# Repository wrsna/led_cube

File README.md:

# led_cube
This is project that was created 2015 with my friend we decided it will be cool to make an 8x8x8 RGB led cube, so we put heads together and figure it out.

All files are created with Eagle software it is more or less schematic and board view and backup files 

there are some images of the finished product and sadly no Arduino code to see it working that is still waiting to be written

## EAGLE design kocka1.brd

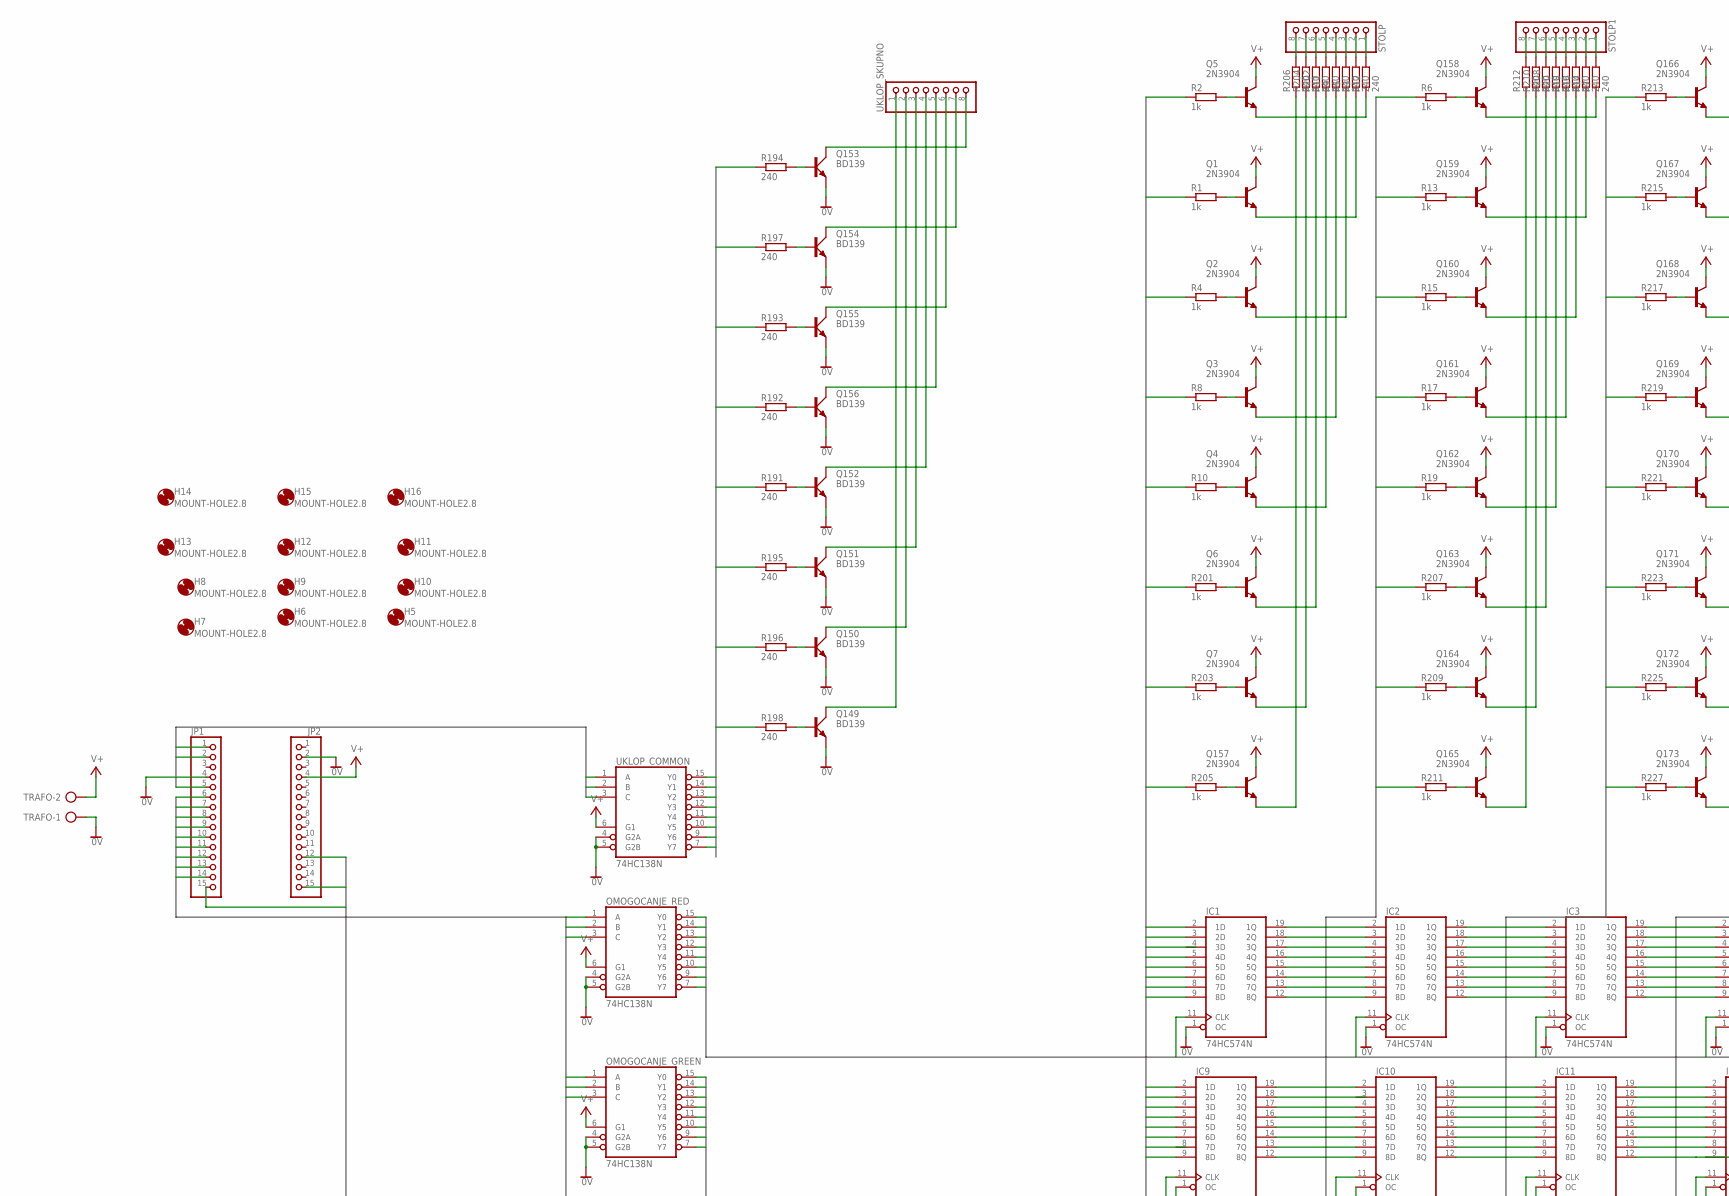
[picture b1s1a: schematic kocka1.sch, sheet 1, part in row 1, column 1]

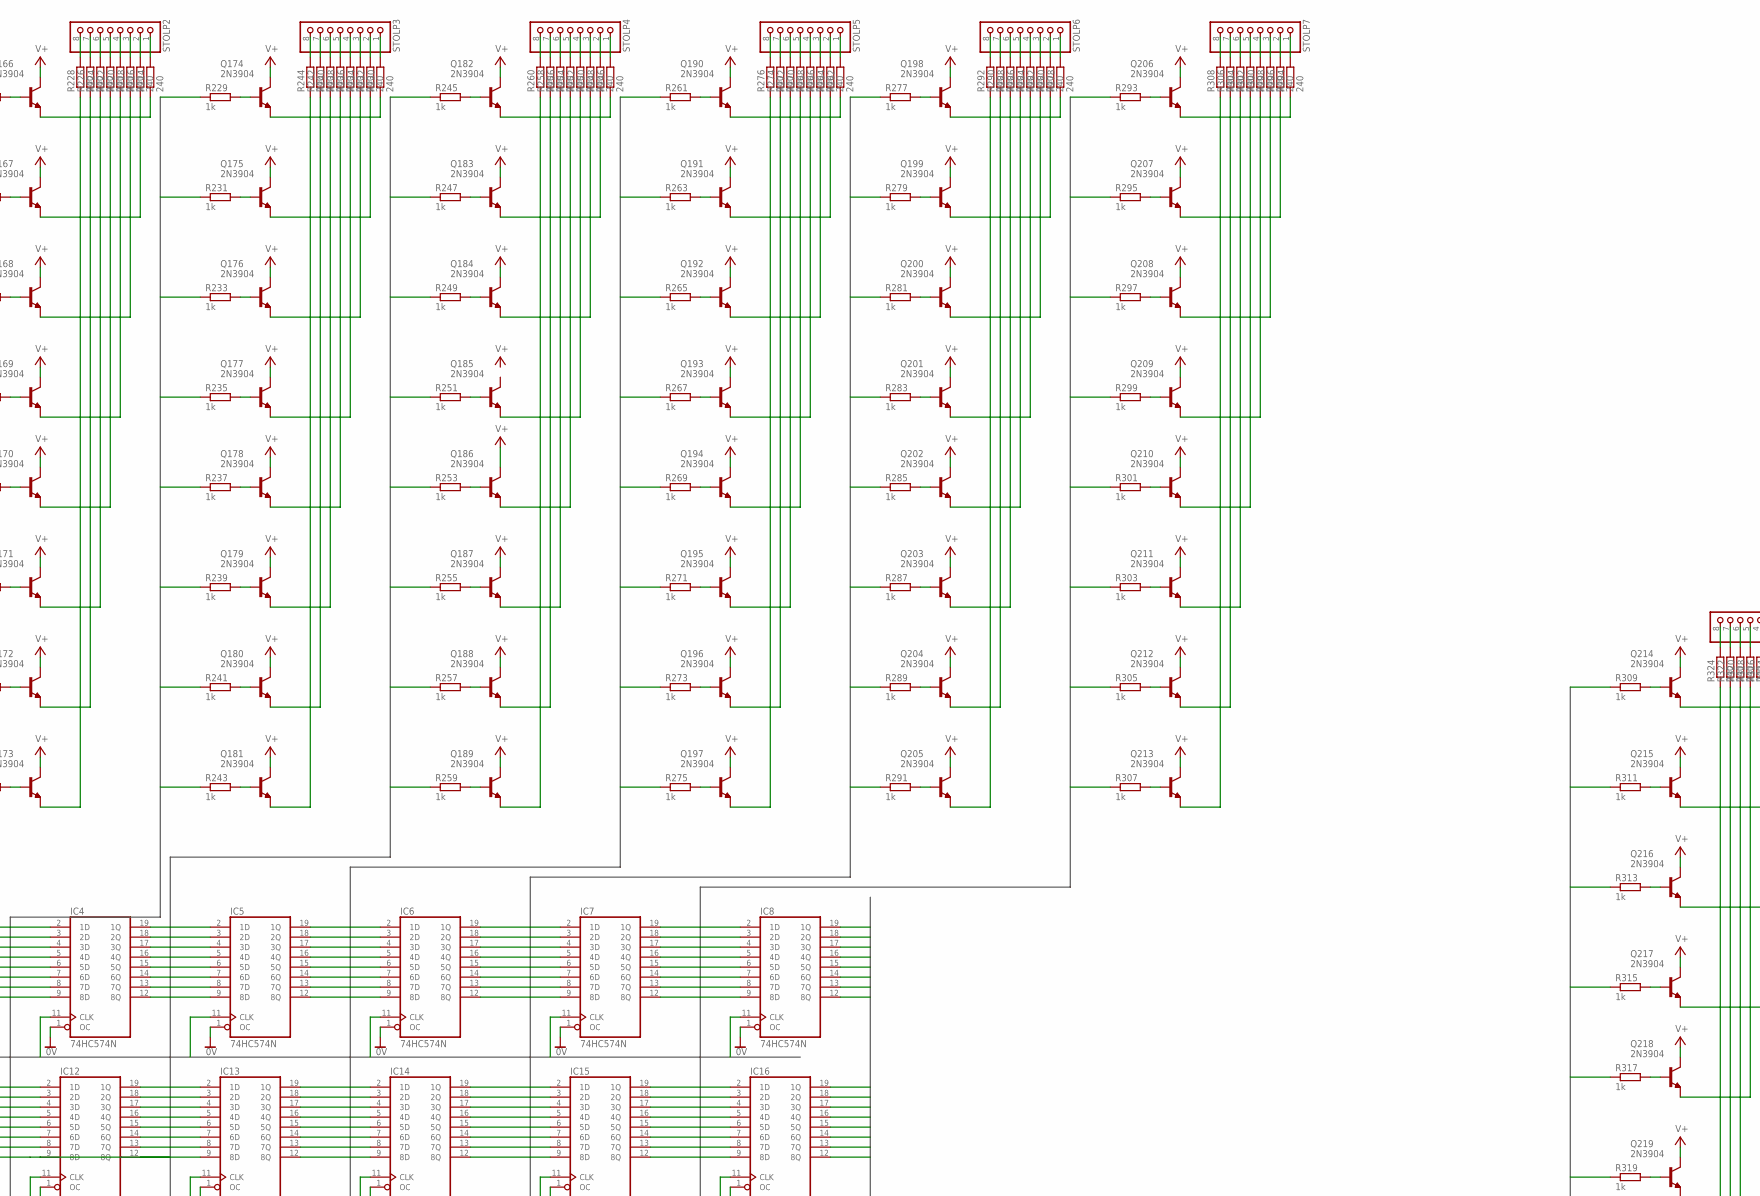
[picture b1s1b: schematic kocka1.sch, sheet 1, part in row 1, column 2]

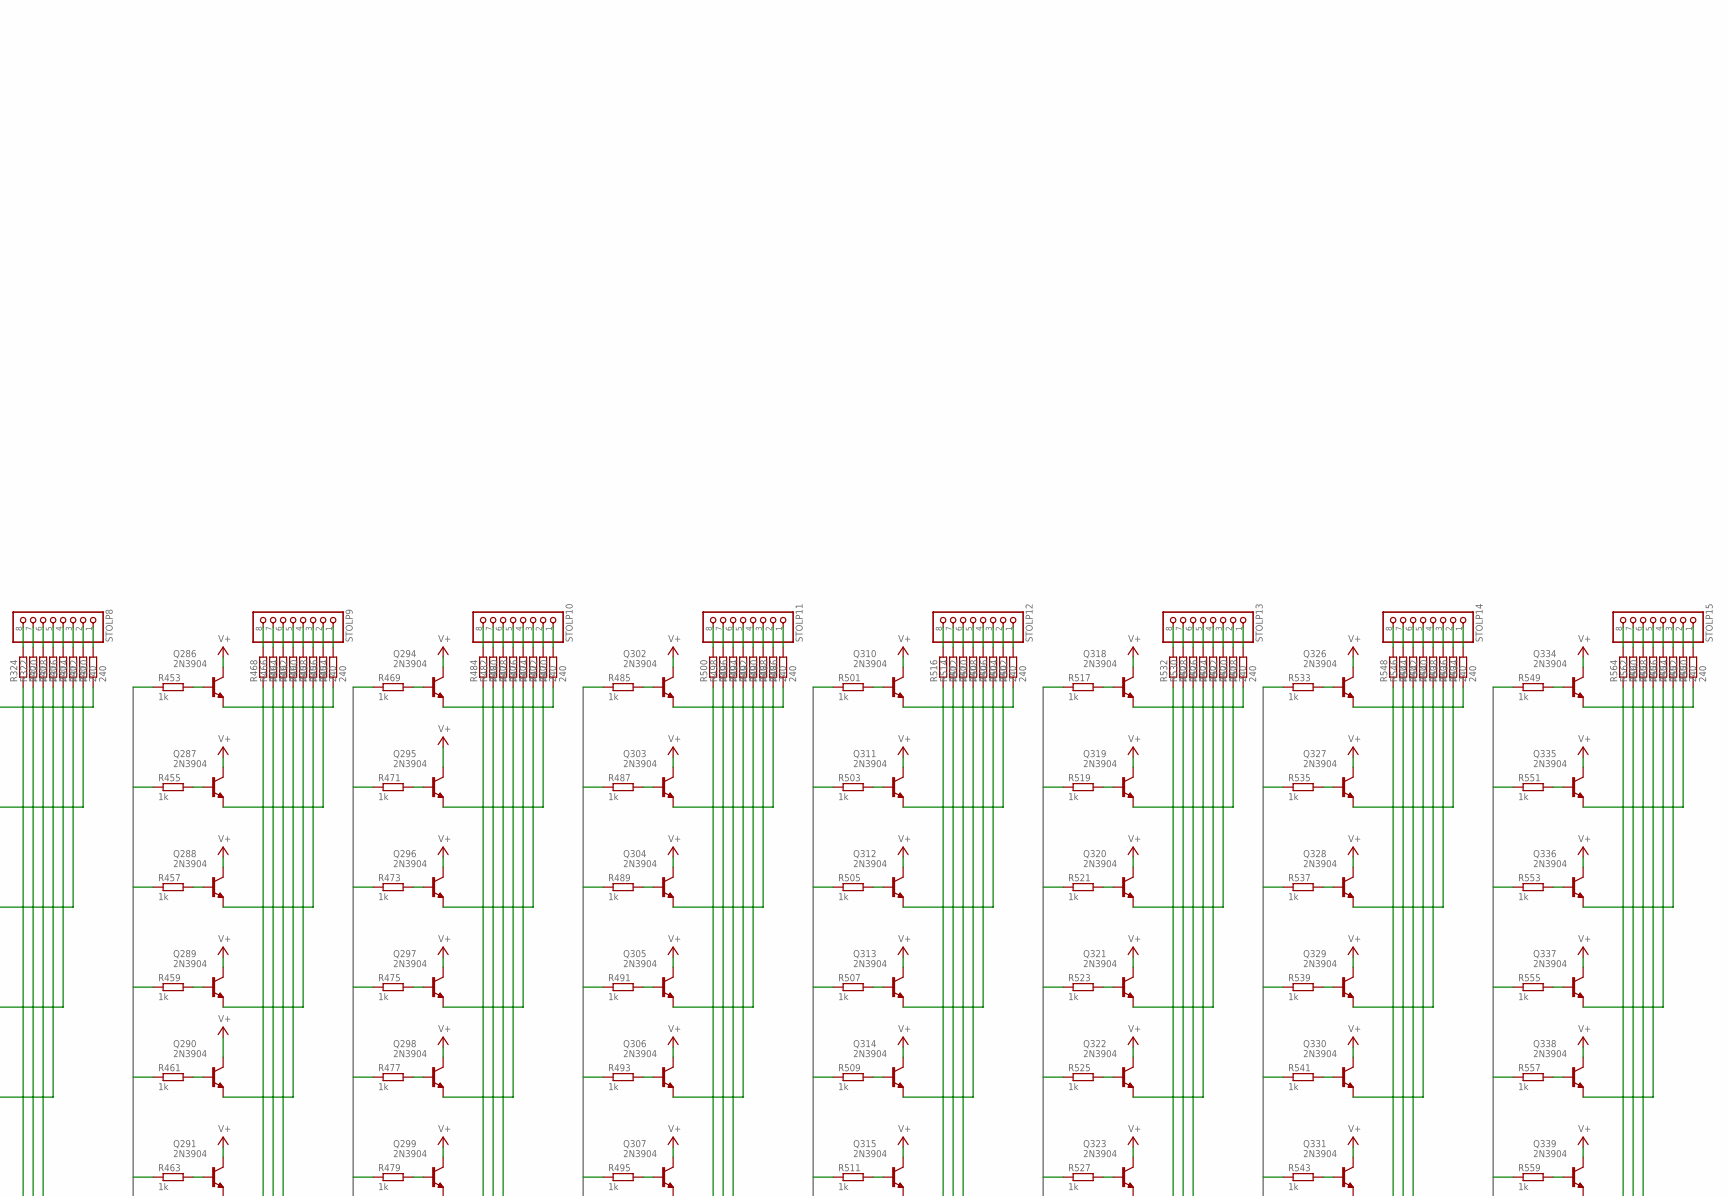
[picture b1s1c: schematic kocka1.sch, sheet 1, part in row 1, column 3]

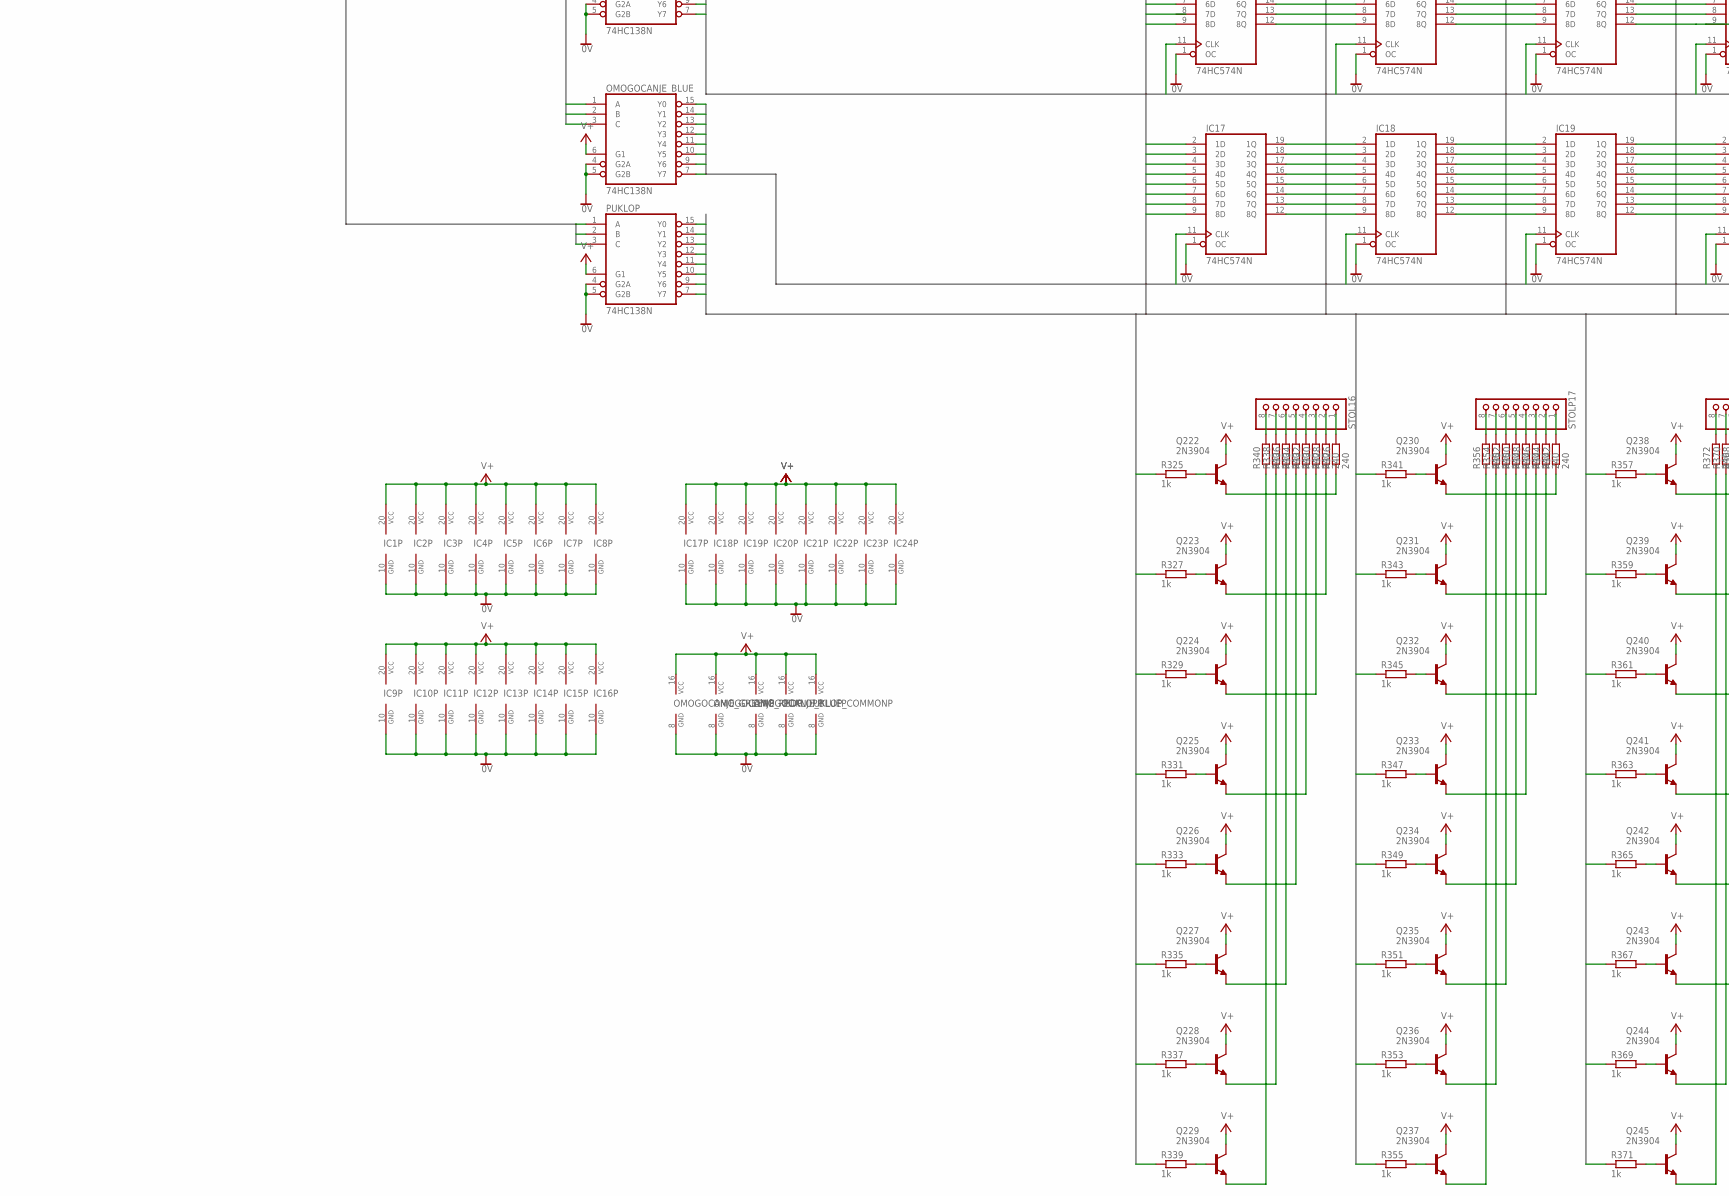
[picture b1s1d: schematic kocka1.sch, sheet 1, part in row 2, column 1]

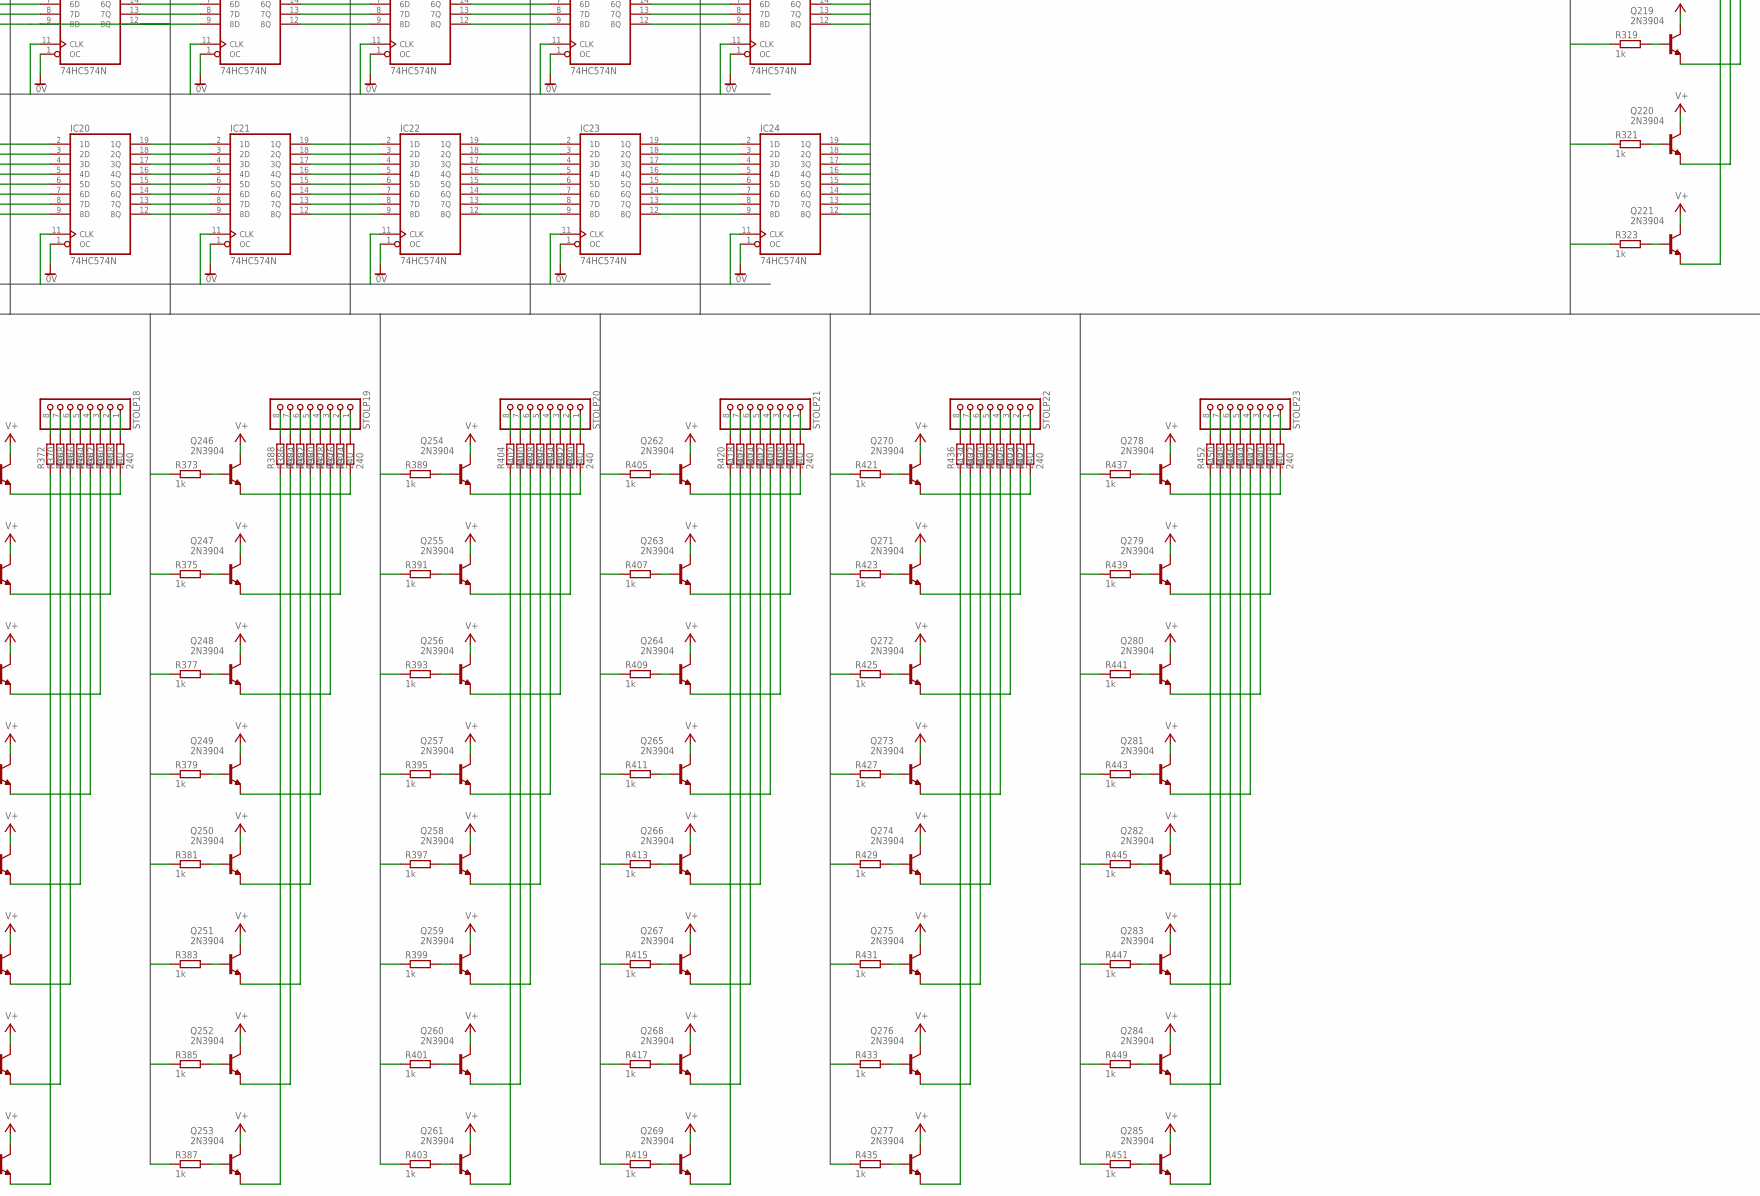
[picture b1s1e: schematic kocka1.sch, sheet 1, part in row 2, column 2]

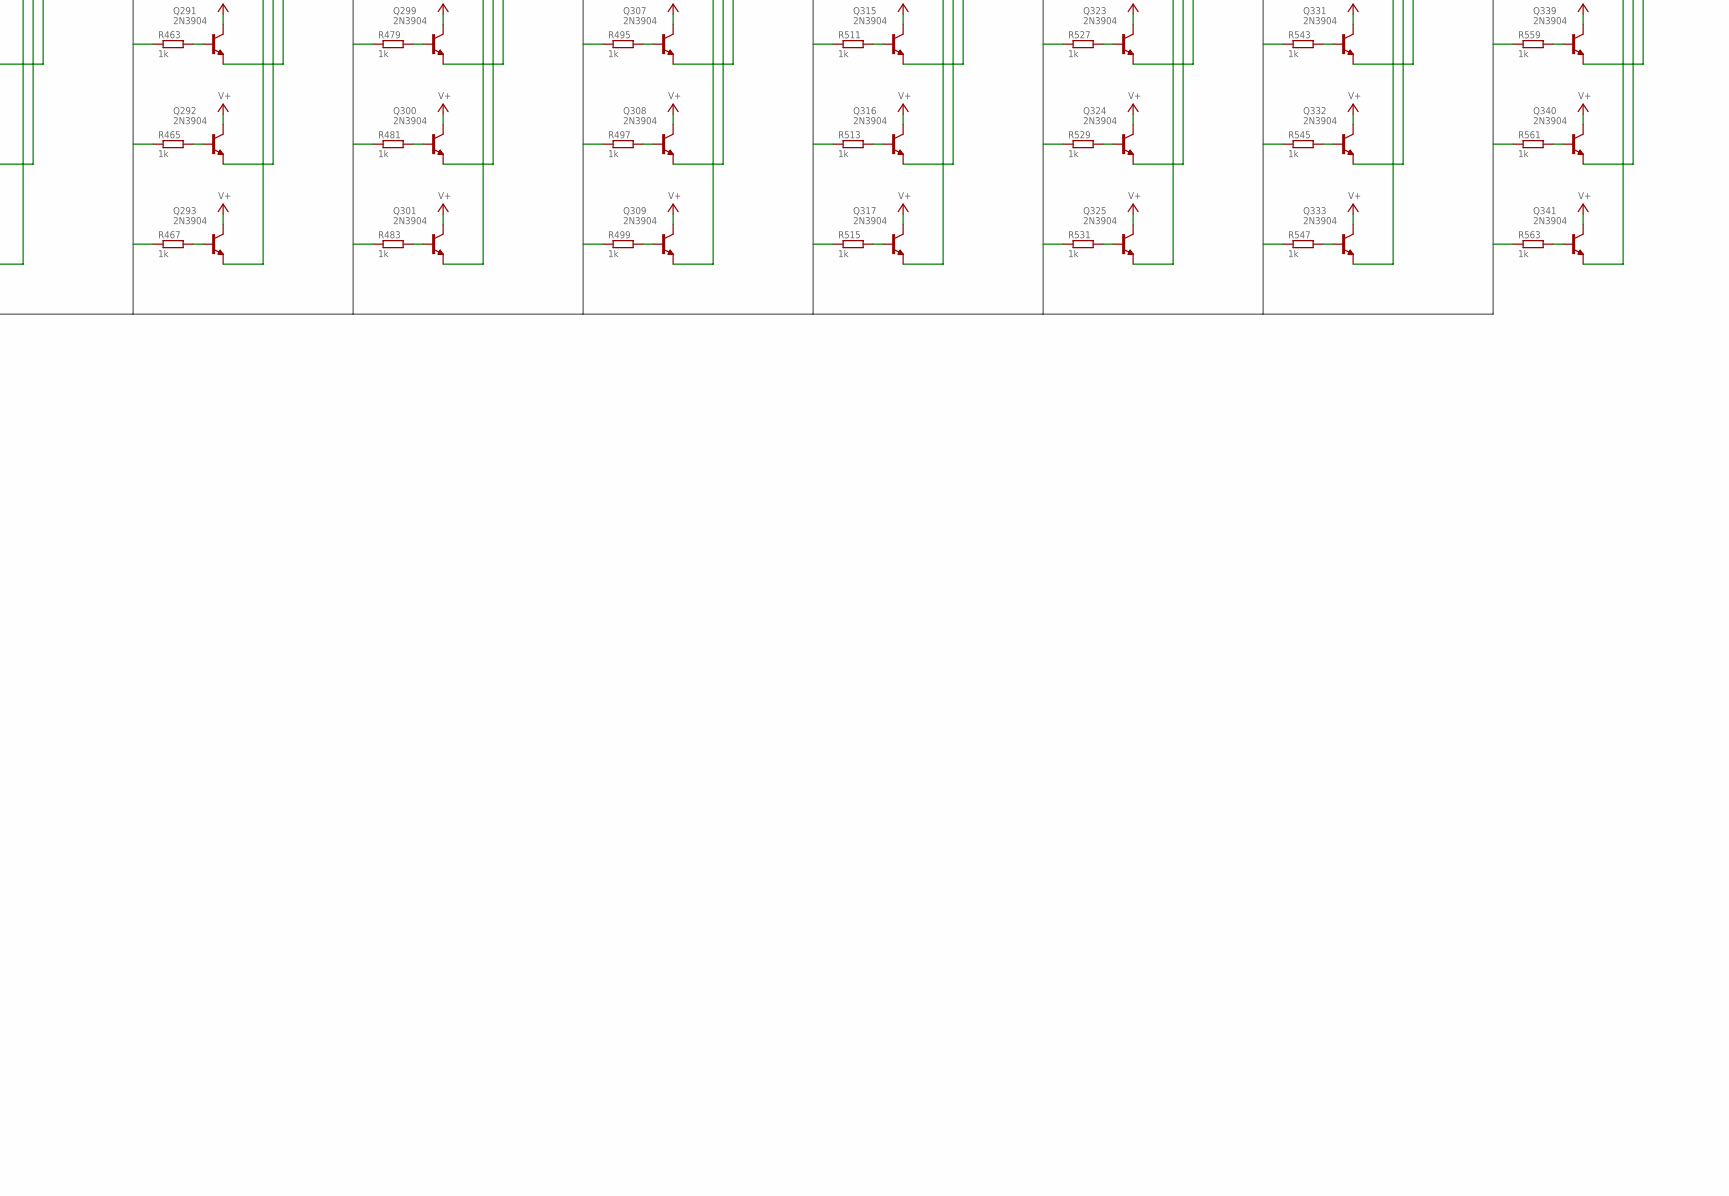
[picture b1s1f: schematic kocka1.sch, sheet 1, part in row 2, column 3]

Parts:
H5, H6, H7, H8, H9, H10, H11, H12, H13, H14, H15, H16: MOUNT-HOLE2.8; 2,8
IC1, IC2, IC3, IC4, IC5, IC6, IC7, IC8, IC9, IC10, IC11, IC12, IC13, IC14, IC15, IC16, IC17, IC18, IC19, IC20, IC21, IC22, IC23, IC24: 74HC574N; DIL20
JP1, JP2: PINHD-1X15; 1X15
OMOGOCANJE_BLUE: 74HC138N; DIL16
OMOGOCANJE_GREEN: 74HC138N; DIL16
OMOGOCANJE_RED: 74HC138N; DIL16
PUKLOP: 74HC138N; DIL16
Q1, Q2, Q3, Q4, Q5, Q6, Q7, Q157, Q158, Q159, Q160, Q161, Q162, Q163, Q164, Q165, Q166, Q167, Q168, Q169, Q170, Q171, Q172, Q173, Q174, Q175, Q176, Q177, Q178, Q179, Q180, Q181, Q182, Q183, Q184, Q185, Q186, Q187, Q188, Q189, Q190, Q191, Q192, Q193, Q194, Q195, Q196, Q197, Q198, Q199, Q200, Q201, Q202, Q203, Q204, Q205, Q206, Q207, Q208, Q209, Q210, Q211, Q212, Q213, Q214, Q215, Q216, Q217, Q218, Q219, Q220, Q221, Q222, Q223, Q224, Q225, Q226, Q227, Q228, Q229, Q230, Q231, Q232, Q233, Q234, Q235, Q236, Q237, Q238, Q239, Q240, Q241, Q242, Q243, Q244, Q245, Q246, Q247, Q248, Q249, Q250, Q251, Q252, Q253, Q254, Q255, Q256, Q257, Q258, Q259, Q260, Q261, Q262, Q263, Q264, Q265, Q266, Q267, Q268, Q269, Q270, Q271, Q272, Q273, Q274, Q275, Q276, Q277, Q278, Q279, Q280, Q281, Q282, Q283, Q284, Q285, Q286, Q287, Q288, Q289, Q290, Q291, Q292, Q293, Q294, Q295, Q296, Q297, Q298, Q299, Q300, Q301, Q302, Q303, Q304, Q305, Q306, Q307, Q308, Q309, Q310, Q311, Q312, Q313, Q314, Q315, Q316, Q317, Q318, Q319, Q320, Q321, Q322, Q323, Q324, Q325, Q326, Q327, Q328, Q329, Q330, Q331, Q332, Q333, Q334, Q335, Q336, Q337, Q338, Q339, Q340, Q341: 2N3904; TO92
Q149, Q150, Q151, Q152, Q153, Q154, Q155, Q156: BD139; TO126AV
R1, R2, R4, R6, R8, R10, R13, R15, R17, R19, R201, R203, R205, R207, R209, R211, R213, R215, R217, R219, R221, R223, R225, R227, R229, R231, R233, R235, R237, R239, R241, R243, R245, R247, R249, R251, R253, R255, R257, R259, R261, R263, R265, R267, R269, R271, R273, R275, R277, R279, R281, R283, R285, R287, R289, R291, R293, R295, R297, R299, R301, R303, R305, R307, R309, R311, R313, R315, R317, R319, R321, R323, R325, R327, R329, R331, R333, R335, R337, R339, R341, R343, R345, R347, R349, R351, R353, R355, R357, R359, R361, R363, R365, R367, R369, R371, R373, R375, R377, R379, R381, R383, R385, R387, R389, R391, R393, R395, R397, R399, R401, R403, R405, R407, R409, R411, R413, R415, R417, R419, R421, R423, R425, R427, R429, R431, R433, R435, R437, R439, R441, R443, R445, R447, R449, R451, R453, R455, R457, R459, R461, R463, R465, R467, R469, R471, R473, R475, R477, R479, R481, R483, R485, R487, R489, R491, R493, R495, R497, R499, R501, R503, R505, R507, R509, R511, R513, R515, R517, R519, R521, R523, R525, R527, R529, R531, R533, R535, R537, R539, R541, R543, R545, R547, R549, R551, R553, R555, R557, R559, R561, R563: 1k; 0207/10
R3, R5, R7, R9, R11, R12, R14, R16, R18, R20, R191, R192, R193, R194, R195, R196, R197, R198, R202, R204, R206, R208, R210, R212, R214, R216, R218, R220, R222, R224, R226, R228, R230, R232, R234, R236, R238, R240, R242, R244, R246, R248, R250, R252, R254, R256, R258, R260, R262, R264, R266, R268, R270, R272, R274, R276, R278, R280, R282, R284, R286, R288, R290, R292, R294, R296, R298, R300, R302, R304, R306, R308, R310, R312, R314, R316, R318, R320, R322, R324, R326, R328, R330, R332, R334, R336, R338, R340, R342, R344, R346, R348, R350, R352, R354, R356, R358, R360, R362, R364, R366, R368, R370, R372, R374, R376, R378, R380, R382, R384, R386, R388, R390, R392, R394, R396, R398, R400, R402, R404, R406, R408, R410, R412, R414, R416, R418, R420, R422, R424, R426, R428, R430, R432, R434, R436, R438, R440, R442, R444, R446, R448, R450, R452, R454, R456, R458, R460, R462, R464, R466, R468, R470, R472, R474, R476, R478, R480, R482, R484, R486, R488, R490, R492, R494, R496, R498, R500, R502, R504, R506, R508, R510, R512, R514, R516, R518, R520, R522, R524, R526, R528, R530, R532, R534, R536, R538, R540, R542, R544, R546, R548, R550, R552, R554, R556, R558, R560, R562, R564: 240; 0207/10
STOL16: PINHD-1X8; 1X08
STOLP, STOLP1, STOLP2, STOLP3, STOLP4, STOLP5, STOLP6, STOLP7, STOLP8, STOLP9, STOLP10, STOLP11, STOLP12, STOLP13, STOLP14, STOLP15, STOLP17, STOLP18, STOLP19, STOLP20, STOLP21, STOLP22, STOLP23: PINHD-1X8; 1X08
TRAFO: AK300/2
UKLOP_COMMON: 74HC138N; DIL16
UKLOP_SKUPNO: PINHD-1X8; 1X08

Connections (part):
0V: IC1.1 (OC), IC1.10 (GND), IC2.1 (OC), IC2.10 (GND), IC3.1 (OC), IC3.10 (GND), IC4.1 (OC), IC4.10 (GND), IC5.1 (OC), IC5.10 (GND), IC6.1 (OC), IC6.10 (GND), IC7.1 (OC), IC7.10 (GND), IC8.1 (OC), IC8.10 (GND), IC9.1 (OC), IC9.10 (GND), IC10.1 (OC), IC10.10 (GND), IC11.1 (OC), IC11.10 (GND), IC12.1 (OC), IC12.10 (GND), IC13.1 (OC), IC13.10 (GND), IC14.1 (OC), IC14.10 (GND), IC15.1 (OC), IC15.10 (GND), IC16.1 (OC), IC16.10 (GND), IC17.1 (OC), IC17.10 (GND), IC18.1 (OC), IC18.10 (GND), IC19.1 (OC), IC19.10 (GND), IC20.1 (OC), IC20.10 (GND), IC21.1 (OC), IC21.10 (GND), IC22.1 (OC), IC22.10 (GND), IC23.1 (OC), IC23.10 (GND), IC24.1 (OC), IC24.10 (GND), JP1.4, JP2.2, OMOGOCANJE_BLUE.4 (G2A), OMOGOCANJE_BLUE.5 (G2B), OMOGOCANJE_BLUE.8 (GND), OMOGOCANJE_GREEN.4 (G2A), OMOGOCANJE_GREEN.5 (G2B), OMOGOCANJE_GREEN.8 (GND), OMOGOCANJE_RED.4 (G2A), OMOGOCANJE_RED.5 (G2B), OMOGOCANJE_RED.8 (GND), PUKLOP.4 (G2A), PUKLOP.5 (G2B), PUKLOP.8 (GND), Q149.E, Q150.E, Q151.E, Q152.E, Q153.E, Q154.E, Q155.E, Q156.E, TRAFO.1, UKLOP_COMMON.4 (G2A), UKLOP_COMMON.5 (G2B), UKLOP_COMMON.8 (GND)
COMMON0: JP1.2, UKLOP_COMMON.3 (C)
COMMON1: JP1.1, UKLOP_COMMON.2 (B)
COMMON2: JP1.5, UKLOP_COMMON.1 (A)
unnamed: Q149.B, R198.2
unnamed: Q5.3 (E), R12.1
unnamed: Q150.B, R196.2
unnamed: Q151.B, R195.2
unnamed: Q152.B, R191.2
unnamed: Q156.B, R192.2
unnamed: Q155.B, R193.2
unnamed: Q154.B, R197.2
unnamed: Q153.B, R194.2
unnamed: Q153.C, UKLOP_SKUPNO.8
unnamed: Q154.C, UKLOP_SKUPNO.7
unnamed: Q155.C, UKLOP_SKUPNO.6
unnamed: Q156.C, UKLOP_SKUPNO.5
unnamed: Q152.C, UKLOP_SKUPNO.4
unnamed: Q151.C, UKLOP_SKUPNO.3
unnamed: Q150.C, UKLOP_SKUPNO.2
unnamed: Q149.C, UKLOP_SKUPNO.1
unnamed: Q5.2 (B), R2.2
unnamed: Q1.2 (B), R1.2
unnamed: Q1.3 (E), R3.1
unnamed: Q2.2 (B), R4.2
unnamed: Q2.3 (E), R5.1
unnamed: Q3.2 (B), R8.2
unnamed: Q3.3 (E), R9.1
unnamed: Q4.2 (B), R10.2
unnamed: Q4.3 (E), R11.1
unnamed: Q6.2 (B), R201.2
unnamed: Q6.3 (E), R202.1
unnamed: Q7.2 (B), R203.2
unnamed: Q7.3 (E), R204.1
unnamed: Q157.2 (B), R205.2
unnamed: Q157.3 (E), R206.1
unnamed: Q158.3 (E), R7.1
unnamed: Q159.3 (E), R14.1
unnamed: Q160.3 (E), R16.1
unnamed: Q161.3 (E), R18.1
unnamed: Q162.3 (E), R20.1
unnamed: Q163.3 (E), R208.1
unnamed: Q164.3 (E), R210.1
unnamed: Q165.3 (E), R212.1
unnamed: Q158.2 (B), R6.2
unnamed: R212.2, STOLP1.8
unnamed: Q159.2 (B), R13.2
unnamed: R210.2, STOLP1.7
unnamed: Q160.2 (B), R15.2
unnamed: R208.2, STOLP1.6
unnamed: Q161.2 (B), R17.2
unnamed: R20.2, STOLP1.5
unnamed: Q162.2 (B), R19.2
unnamed: R18.2, STOLP1.4
unnamed: Q163.2 (B), R207.2
unnamed: R16.2, STOLP1.3
unnamed: Q164.2 (B), R209.2
unnamed: R14.2, STOLP1.2
unnamed: Q165.2 (B), R211.2
unnamed: R7.2, STOLP1.1
unnamed: R206.2, STOLP.8
unnamed: R204.2, STOLP.7
unnamed: R202.2, STOLP.6
unnamed: R11.2, STOLP.5
unnamed: R9.2, STOLP.4
unnamed: R5.2, STOLP.3
unnamed: R3.2, STOLP.2
unnamed: R12.2, STOLP.1
unnamed: Q166.2 (B), R213.2
unnamed: R228.2, STOLP2.8
unnamed: Q167.2 (B), R215.2
unnamed: R226.2, STOLP2.7
unnamed: Q168.2 (B), R217.2
unnamed: R224.2, STOLP2.6
unnamed: Q169.2 (B), R219.2
unnamed: R222.2, STOLP2.5
unnamed: Q170.2 (B), R221.2
unnamed: R220.2, STOLP2.4
unnamed: Q171.2 (B), R223.2
unnamed: R218.2, STOLP2.3
unnamed: Q172.2 (B), R225.2
unnamed: R216.2, STOLP2.2
unnamed: Q173.2 (B), R227.2
unnamed: R214.2, STOLP2.1
unnamed: Q166.3 (E), R214.1
unnamed: Q167.3 (E), R216.1
unnamed: Q168.3 (E), R218.1
unnamed: Q169.3 (E), R220.1
unnamed: Q170.3 (E), R222.1
unnamed: Q171.3 (E), R224.1
unnamed: Q172.3 (E), R226.1
unnamed: Q173.3 (E), R228.1
unnamed: Q174.2 (B), R229.2
unnamed: Q174.3 (E), R230.1
unnamed: Q175.2 (B), R231.2
unnamed: R244.2, STOLP3.8
unnamed: Q176.2 (B), R233.2
unnamed: R242.2, STOLP3.7
unnamed: Q177.2 (B), R235.2
unnamed: R240.2, STOLP3.6
unnamed: Q178.2 (B), R237.2
unnamed: R238.2, STOLP3.5
unnamed: Q179.2 (B), R239.2
unnamed: R236.2, STOLP3.4
unnamed: Q180.2 (B), R241.2
unnamed: R234.2, STOLP3.3
unnamed: Q181.2 (B), R243.2
unnamed: R232.2, STOLP3.2
unnamed: R230.2, STOLP3.1
unnamed: Q175.3 (E), R232.1
unnamed: Q176.3 (E), R234.1
unnamed: Q177.3 (E), R236.1
unnamed: Q178.3 (E), R238.1
unnamed: Q179.3 (E), R240.1
unnamed: Q180.3 (E), R242.1
unnamed: Q181.3 (E), R244.1
unnamed: Q182.2 (B), R245.2
unnamed: Q182.3 (E), R246.1
unnamed: Q183.2 (B), R247.2
unnamed: R260.2, STOLP4.8
unnamed: Q184.2 (B), R249.2
unnamed: R258.2, STOLP4.7
unnamed: Q185.2 (B), R251.2
unnamed: R256.2, STOLP4.6
unnamed: Q186.2 (B), R253.2
unnamed: R254.2, STOLP4.5
unnamed: Q187.2 (B), R255.2
unnamed: R252.2, STOLP4.4
unnamed: Q188.2 (B), R257.2
unnamed: R250.2, STOLP4.3
unnamed: Q189.2 (B), R259.2
unnamed: R248.2, STOLP4.2
unnamed: Q183.3 (E), R248.1
unnamed: Q184.3 (E), R250.1
unnamed: R246.2, STOLP4.1
unnamed: Q185.3 (E), R252.1
unnamed: Q186.3 (E), R254.1
unnamed: Q187.3 (E), R256.1
unnamed: Q188.3 (E), R258.1
unnamed: Q189.3 (E), R260.1
unnamed: Q190.2 (B), R261.2
unnamed: R276.2, STOLP5.8
unnamed: Q191.2 (B), R263.2
unnamed: R274.2, STOLP5.7
unnamed: Q192.2 (B), R265.2
unnamed: R272.2, STOLP5.6
unnamed: Q193.2 (B), R267.2
unnamed: R270.2, STOLP5.5
unnamed: Q194.2 (B), R269.2
unnamed: R268.2, STOLP5.4
unnamed: Q195.2 (B), R271.2
unnamed: R266.2, STOLP5.3
unnamed: Q196.2 (B), R273.2
unnamed: R264.2, STOLP5.2
unnamed: Q197.2 (B), R275.2
unnamed: R262.2, STOLP5.1
unnamed: Q190.3 (E), R262.1
unnamed: Q191.3 (E), R264.1
unnamed: Q192.3 (E), R266.1
unnamed: Q193.3 (E), R268.1
unnamed: Q194.3 (E), R270.1
unnamed: Q195.3 (E), R272.1
unnamed: Q196.3 (E), R274.1
unnamed: Q197.3 (E), R276.1
unnamed: Q198.2 (B), R277.2
unnamed: R292.2, STOLP6.8
unnamed: Q199.2 (B), R279.2
unnamed: R290.2, STOLP6.7
unnamed: Q200.2 (B), R281.2
unnamed: R288.2, STOLP6.6
unnamed: Q201.2 (B), R283.2
unnamed: R286.2, STOLP6.5
unnamed: Q202.2 (B), R285.2
unnamed: R284.2, STOLP6.4
unnamed: Q203.2 (B), R287.2
unnamed: R282.2, STOLP6.3
unnamed: Q204.2 (B), R289.2
unnamed: R280.2, STOLP6.2
unnamed: Q205.2 (B), R291.2
unnamed: R278.2, STOLP6.1
unnamed: Q198.3 (E), R278.1
unnamed: Q199.3 (E), R280.1
unnamed: Q200.3 (E), R282.1
unnamed: Q201.3 (E), R284.1
unnamed: Q202.3 (E), R286.1
unnamed: Q203.3 (E), R288.1
unnamed: Q204.3 (E), R290.1
unnamed: Q205.3 (E), R292.1
unnamed: Q206.2 (B), R293.2
unnamed: Q206.3 (E), R294.1
unnamed: Q207.2 (B), R295.2
unnamed: R308.2, STOLP7.8
unnamed: Q208.2 (B), R297.2
unnamed: R306.2, STOLP7.7
unnamed: Q209.2 (B), R299.2
unnamed: R304.2, STOLP7.6
unnamed: Q210.2 (B), R301.2
unnamed: R302.2, STOLP7.5
unnamed: Q211.2 (B), R303.2
unnamed: R300.2, STOLP7.4
unnamed: Q212.2 (B), R305.2
unnamed: R298.2, STOLP7.3
unnamed: Q213.2 (B), R307.2
unnamed: R296.2, STOLP7.2
unnamed: R294.2, STOLP7.1
unnamed: Q207.3 (E), R296.1
unnamed: Q208.3 (E), R298.1
unnamed: Q209.3 (E), R300.1
unnamed: Q210.3 (E), R302.1
unnamed: Q211.3 (E), R304.1
unnamed: Q212.3 (E), R306.1
unnamed: Q213.3 (E), R308.1
unnamed: Q214.2 (B), R309.2
unnamed: R324.2, STOLP8.8
unnamed: Q215.2 (B), R311.2
unnamed: R322.2, STOLP8.7
unnamed: Q216.2 (B), R313.2
unnamed: R320.2, STOLP8.6
unnamed: Q217.2 (B), R315.2
unnamed: R318.2, STOLP8.5
unnamed: Q218.2 (B), R317.2
unnamed: R316.2, STOLP8.4
unnamed: Q219.2 (B), R319.2
unnamed: R314.2, STOLP8.3
unnamed: Q220.2 (B), R321.2
unnamed: R312.2, STOLP8.2
unnamed: Q221.2 (B), R323.2
unnamed: R310.2, STOLP8.1
unnamed: Q214.3 (E), R310.1
unnamed: Q215.3 (E), R312.1
unnamed: Q216.3 (E), R314.1
unnamed: Q217.3 (E), R316.1
unnamed: Q218.3 (E), R318.1
unnamed: Q219.3 (E), R320.1
unnamed: Q220.3 (E), R322.1
unnamed: Q221.3 (E), R324.1
unnamed: Q222.2 (B), R325.2
unnamed: Q286.3 (E), R454.1
unnamed: Q223.2 (B), R327.2
unnamed: R468.2, STOLP9.8
unnamed: Q224.2 (B), R329.2
unnamed: R466.2, STOLP9.7
unnamed: Q225.2 (B), R331.2
unnamed: R464.2, STOLP9.6
unnamed: Q226.2 (B), R333.2
unnamed: R462.2, STOLP9.5
unnamed: Q227.2 (B), R335.2
unnamed: R460.2, STOLP9.4
unnamed: Q228.2 (B), R337.2
unnamed: R458.2, STOLP9.3
unnamed: Q229.2 (B), R339.2
unnamed: R456.2, STOLP9.2
unnamed: R454.2, STOLP9.1
unnamed: Q287.3 (E), R456.1
unnamed: Q288.3 (E), R458.1
unnamed: Q289.3 (E), R460.1
unnamed: Q290.3 (E), R462.1
unnamed: Q291.3 (E), R464.1
unnamed: Q292.3 (E), R466.1
unnamed: Q293.3 (E), R468.1
unnamed: Q230.2 (B), R341.2
unnamed: Q294.3 (E), R470.1
unnamed: Q231.2 (B), R343.2
unnamed: R484.2, STOLP10.8
unnamed: Q232.2 (B), R345.2
unnamed: R482.2, STOLP10.7
unnamed: Q233.2 (B), R347.2
unnamed: R480.2, STOLP10.6
unnamed: Q234.2 (B), R349.2
unnamed: R478.2, STOLP10.5
unnamed: Q235.2 (B), R351.2
unnamed: R476.2, STOLP10.4
unnamed: Q236.2 (B), R353.2
unnamed: R474.2, STOLP10.3
unnamed: Q237.2 (B), R355.2
unnamed: R472.2, STOLP10.2
unnamed: R470.2, STOLP10.1
unnamed: Q295.3 (E), R472.1
unnamed: Q296.3 (E), R474.1
unnamed: Q297.3 (E), R476.1
unnamed: Q298.3 (E), R478.1
unnamed: Q299.3 (E), R480.1
unnamed: Q300.3 (E), R482.1
unnamed: Q301.3 (E), R484.1
unnamed: Q238.2 (B), R357.2
unnamed: R500.2, STOLP11.8
unnamed: Q239.2 (B), R359.2
unnamed: R498.2, STOLP11.7
unnamed: Q240.2 (B), R361.2
unnamed: R496.2, STOLP11.6
unnamed: Q241.2 (B), R363.2
unnamed: R494.2, STOLP11.5
unnamed: Q242.2 (B), R365.2
unnamed: R492.2, STOLP11.4
unnamed: Q243.2 (B), R367.2
unnamed: R490.2, STOLP11.3
unnamed: Q244.2 (B), R369.2
unnamed: R488.2, STOLP11.2
unnamed: Q245.2 (B), R371.2
unnamed: R486.2, STOLP11.1
unnamed: Q302.3 (E), R486.1
unnamed: Q303.3 (E), R488.1
unnamed: Q304.3 (E), R490.1
unnamed: Q305.3 (E), R492.1
unnamed: Q306.3 (E), R494.1
unnamed: Q307.3 (E), R496.1
unnamed: Q308.3 (E), R498.1
unnamed: Q246.2 (B), R373.2
unnamed: Q309.3 (E), R500.1
unnamed: Q247.2 (B), R375.2
unnamed: Q310.3 (E), R502.1
unnamed: Q248.2 (B), R377.2
unnamed: R516.2, STOLP12.8
unnamed: Q249.2 (B), R379.2
unnamed: R514.2, STOLP12.7
unnamed: Q250.2 (B), R381.2
unnamed: R512.2, STOLP12.6
unnamed: Q251.2 (B), R383.2
unnamed: R510.2, STOLP12.5
unnamed: Q252.2 (B), R385.2
unnamed: R508.2, STOLP12.4
unnamed: Q253.2 (B), R387.2
unnamed: R506.2, STOLP12.3
unnamed: R504.2, STOLP12.2
unnamed: R502.2, STOLP12.1
unnamed: Q311.3 (E), R504.1
unnamed: Q312.3 (E), R506.1
unnamed: Q313.3 (E), R508.1
unnamed: Q314.3 (E), R510.1
unnamed: Q315.3 (E), R512.1
unnamed: Q316.3 (E), R514.1
unnamed: Q254.2 (B), R389.2
unnamed: Q317.3 (E), R516.1
unnamed: Q255.2 (B), R391.2
unnamed: Q318.3 (E), R518.1
unnamed: Q256.2 (B), R393.2
unnamed: Q319.3 (E), R520.1
unnamed: Q257.2 (B), R395.2
unnamed: Q320.3 (E), R522.1
unnamed: Q258.2 (B), R397.2
unnamed: Q321.3 (E), R524.1
unnamed: Q259.2 (B), R399.2
unnamed: Q322.3 (E), R526.1
unnamed: Q260.2 (B), R401.2
unnamed: Q323.3 (E), R528.1
unnamed: Q261.2 (B), R403.2
unnamed: Q324.3 (E), R530.1
unnamed: Q325.3 (E), R532.1
unnamed: Q326.3 (E), R534.1
unnamed: R532.2, STOLP13.8
unnamed: R530.2, STOLP13.7
unnamed: R528.2, STOLP13.6
unnamed: R526.2, STOLP13.5
unnamed: R524.2, STOLP13.4
unnamed: R522.2, STOLP13.3
unnamed: Q262.2 (B), R405.2
unnamed: R520.2, STOLP13.2
unnamed: Q263.2 (B), R407.2
unnamed: R518.2, STOLP13.1
unnamed: Q264.2 (B), R409.2
unnamed: R548.2, STOLP14.8
unnamed: Q265.2 (B), R411.2
unnamed: R546.2, STOLP14.7
unnamed: Q266.2 (B), R413.2
unnamed: R544.2, STOLP14.6
unnamed: Q267.2 (B), R415.2
unnamed: R542.2, STOLP14.5
unnamed: Q268.2 (B), R417.2
unnamed: R540.2, STOLP14.4
unnamed: Q269.2 (B), R419.2
unnamed: R538.2, STOLP14.3
unnamed: R536.2, STOLP14.2
unnamed: R534.2, STOLP14.1
unnamed: Q327.3 (E), R536.1
unnamed: Q328.3 (E), R538.1
unnamed: Q329.3 (E), R540.1
unnamed: Q330.3 (E), R542.1
unnamed: Q331.3 (E), R544.1
unnamed: Q332.3 (E), R546.1
unnamed: Q270.2 (B), R421.2
unnamed: Q333.3 (E), R548.1
unnamed: Q271.2 (B), R423.2
unnamed: R564.2, STOLP15.8
unnamed: Q272.2 (B), R425.2
unnamed: R562.2, STOLP15.7
unnamed: Q273.2 (B), R427.2
unnamed: R560.2, STOLP15.6
unnamed: Q274.2 (B), R429.2
unnamed: R558.2, STOLP15.5
unnamed: Q275.2 (B), R431.2
unnamed: R556.2, STOLP15.4
unnamed: Q276.2 (B), R433.2
unnamed: R554.2, STOLP15.3
unnamed: Q277.2 (B), R435.2
unnamed: R552.2, STOLP15.2
unnamed: R550.2, STOLP15.1
unnamed: Q334.3 (E), R550.1
unnamed: Q335.3 (E), R552.1
unnamed: Q336.3 (E), R554.1
unnamed: Q337.3 (E), R556.1
unnamed: Q338.3 (E), R558.1
unnamed: Q339.3 (E), R560.1
unnamed: Q340.3 (E), R562.1
unnamed: Q278.2 (B), R437.2
unnamed: Q341.3 (E), R564.1
unnamed: Q279.2 (B), R439.2
unnamed: Q222.3 (E), R326.1
unnamed: Q280.2 (B), R441.2
unnamed: R340.2, STOL16.8
unnamed: Q281.2 (B), R443.2
unnamed: R338.2, STOL16.7
unnamed: Q282.2 (B), R445.2
unnamed: R336.2, STOL16.6
unnamed: Q283.2 (B), R447.2
unnamed: R334.2, STOL16.5
unnamed: Q284.2 (B), R449.2
unnamed: R332.2, STOL16.4
unnamed: Q285.2 (B), R451.2
unnamed: R330.2, STOL16.3
unnamed: R328.2, STOL16.2
unnamed: R326.2, STOL16.1
unnamed: Q223.3 (E), R328.1
unnamed: Q224.3 (E), R330.1
unnamed: Q225.3 (E), R332.1
unnamed: Q226.3 (E), R334.1
unnamed: Q227.3 (E), R336.1
unnamed: Q228.3 (E), R338.1
unnamed: Q286.2 (B), R453.2
unnamed: Q229.3 (E), R340.1
unnamed: Q287.2 (B), R455.2
unnamed: R356.2, STOLP17.8
unnamed: Q288.2 (B), R457.2
unnamed: R354.2, STOLP17.7
unnamed: Q289.2 (B), R459.2
unnamed: R352.2, STOLP17.6
unnamed: Q290.2 (B), R461.2
unnamed: R350.2, STOLP17.5
unnamed: Q291.2 (B), R463.2
unnamed: R348.2, STOLP17.4
unnamed: Q292.2 (B), R465.2
unnamed: R346.2, STOLP17.3
unnamed: Q293.2 (B), R467.2
unnamed: R344.2, STOLP17.2
unnamed: R342.2, STOLP17.1
unnamed: Q230.3 (E), R342.1
unnamed: Q231.3 (E), R344.1
unnamed: Q232.3 (E), R346.1
unnamed: Q233.3 (E), R348.1
unnamed: Q234.3 (E), R350.1
unnamed: Q235.3 (E), R352.1
unnamed: Q236.3 (E), R354.1
unnamed: Q294.2 (B), R469.2
unnamed: Q237.3 (E), R356.1
unnamed: Q295.2 (B), R471.2
unnamed: R372.2, STOLP18.8
unnamed: Q296.2 (B), R473.2
unnamed: R370.2, STOLP18.7
unnamed: Q297.2 (B), R475.2
unnamed: R368.2, STOLP18.6
unnamed: Q298.2 (B), R477.2
unnamed: R366.2, STOLP18.5
unnamed: Q299.2 (B), R479.2
unnamed: R364.2, STOLP18.4
unnamed: Q300.2 (B), R481.2
unnamed: R362.2, STOLP18.3
unnamed: Q301.2 (B), R483.2
unnamed: R360.2, STOLP18.2
unnamed: R358.2, STOLP18.1
unnamed: Q238.3 (E), R358.1
unnamed: Q239.3 (E), R360.1
unnamed: Q240.3 (E), R362.1
unnamed: Q241.3 (E), R364.1
unnamed: Q242.3 (E), R366.1
unnamed: Q243.3 (E), R368.1
unnamed: Q244.3 (E), R370.1
unnamed: Q302.2 (B), R485.2
unnamed: Q245.3 (E), R372.1
unnamed: Q303.2 (B), R487.2
unnamed: R388.2, STOLP19.8
unnamed: Q304.2 (B), R489.2
unnamed: R386.2, STOLP19.7
unnamed: Q305.2 (B), R491.2
unnamed: R384.2, STOLP19.6
unnamed: Q306.2 (B), R493.2
unnamed: R382.2, STOLP19.5
unnamed: Q307.2 (B), R495.2
unnamed: R380.2, STOLP19.4
unnamed: Q308.2 (B), R497.2
unnamed: R378.2, STOLP19.3
unnamed: Q309.2 (B), R499.2
unnamed: R376.2, STOLP19.2
unnamed: R374.2, STOLP19.1
unnamed: Q246.3 (E), R374.1
unnamed: Q247.3 (E), R376.1
unnamed: Q248.3 (E), R378.1
unnamed: Q249.3 (E), R380.1
unnamed: Q250.3 (E), R382.1
unnamed: Q251.3 (E), R384.1
unnamed: Q252.3 (E), R386.1
unnamed: Q310.2 (B), R501.2
unnamed: Q253.3 (E), R388.1
unnamed: Q311.2 (B), R503.2
unnamed: Q254.3 (E), R390.1
unnamed: Q312.2 (B), R505.2
unnamed: R404.2, STOLP20.8
unnamed: Q313.2 (B), R507.2
unnamed: R402.2, STOLP20.7
unnamed: Q314.2 (B), R509.2
unnamed: R400.2, STOLP20.6
unnamed: Q315.2 (B), R511.2
unnamed: R398.2, STOLP20.5
unnamed: Q316.2 (B), R513.2
unnamed: R396.2, STOLP20.4
unnamed: Q317.2 (B), R515.2
unnamed: R394.2, STOLP20.3
unnamed: R392.2, STOLP20.2
unnamed: R390.2, STOLP20.1
unnamed: Q255.3 (E), R392.1
unnamed: Q256.3 (E), R394.1
unnamed: Q257.3 (E), R396.1
unnamed: Q258.3 (E), R398.1
unnamed: Q259.3 (E), R400.1
unnamed: Q260.3 (E), R402.1
unnamed: Q318.2 (B), R517.2
unnamed: Q261.3 (E), R404.1
unnamed: Q319.2 (B), R519.2
unnamed: R420.2, STOLP21.8
unnamed: Q320.2 (B), R521.2
unnamed: R418.2, STOLP21.7
unnamed: Q321.2 (B), R523.2
unnamed: R416.2, STOLP21.6
unnamed: Q322.2 (B), R525.2
unnamed: R414.2, STOLP21.5
unnamed: Q323.2 (B), R527.2
unnamed: R412.2, STOLP21.4
unnamed: Q324.2 (B), R529.2
unnamed: R410.2, STOLP21.3
unnamed: Q325.2 (B), R531.2
unnamed: R408.2, STOLP21.2
unnamed: R406.2, STOLP21.1
unnamed: Q262.3 (E), R406.1
unnamed: Q263.3 (E), R408.1
unnamed: Q264.3 (E), R410.1
unnamed: Q265.3 (E), R412.1
unnamed: Q266.3 (E), R414.1
unnamed: Q267.3 (E), R416.1
unnamed: Q268.3 (E), R418.1
unnamed: Q326.2 (B), R533.2
unnamed: Q269.3 (E), R420.1
unnamed: Q327.2 (B), R535.2
unnamed: Q270.3 (E), R422.1
unnamed: Q328.2 (B), R537.2
unnamed: R436.2, STOLP22.8
unnamed: Q329.2 (B), R539.2
unnamed: R434.2, STOLP22.7
unnamed: Q330.2 (B), R541.2
unnamed: R432.2, STOLP22.6
unnamed: Q331.2 (B), R543.2
unnamed: R430.2, STOLP22.5
unnamed: Q332.2 (B), R545.2
unnamed: R428.2, STOLP22.4
unnamed: Q333.2 (B), R547.2
unnamed: R426.2, STOLP22.3
unnamed: R424.2, STOLP22.2
unnamed: R422.2, STOLP22.1
unnamed: Q271.3 (E), R424.1
unnamed: Q272.3 (E), R426.1
unnamed: Q273.3 (E), R428.1
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
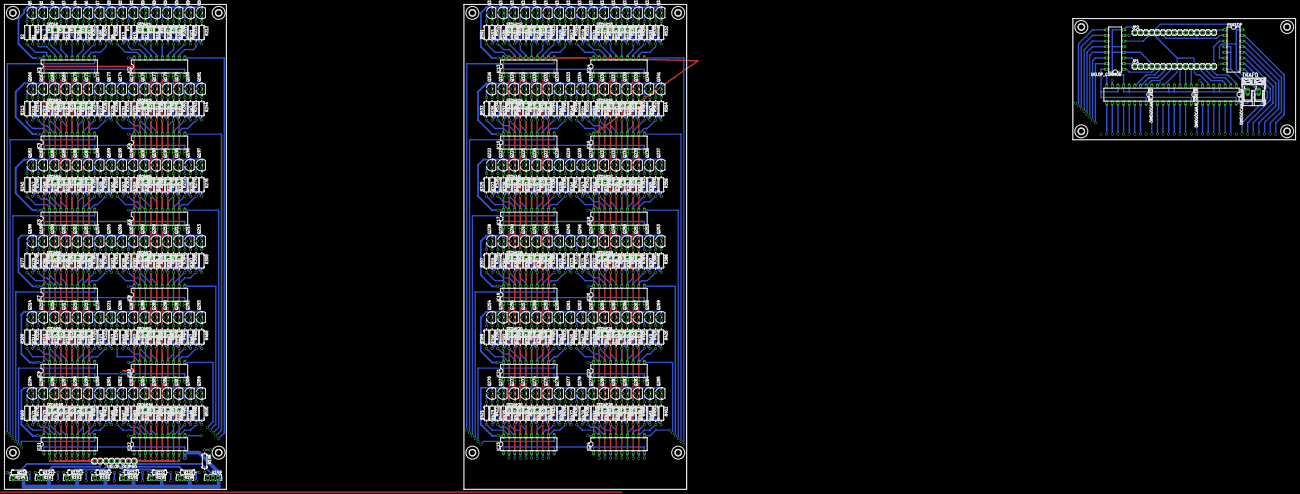
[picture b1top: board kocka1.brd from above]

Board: 2 copper layers, 581.7 x 218.4 mm, 661 parts (0 on the bottom side), 842 nets.
